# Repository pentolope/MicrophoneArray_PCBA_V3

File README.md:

# 16-channel circular PDM microphone array

A 120 mm circular, four-layer KiCad 10 carrier for sixteen `MSM261DHP006` PDM
MEMS microphones running at 3.3 V. A socketed Sipeed Tang Nano 9K performs
acquisition and decimation; a 2012 Raspberry Pi Model B collects the audio over
SPI0 over a 26-way cable to the Pi's P1 header.

The sixteen acoustic ports sit on a 54.00 mm radius at 22.5 degree intervals,
channel 0 on +X, numbered counter-clockwise viewed from the component side.

## Design summary

| | |
|---|---|
| Board | 120 mm circle, 1.6 mm, 4 layers, ENIG, green / white |
| Stackup | signal / GND / GND / signal - both inner layers solid ground |
| Microphones | 16 x `MSM261DHP006`, top-ported, 3.3 V, ports up at the rim |
| Channel pairing | adjacent channels share a data line by clock edge, 8 data nets |
| Reference clock | 24.576 MHz oscillator to a global-clock FPGA pin |
| PDM clock | 3.072 MHz, buffered to 8 series-terminated branches |
| Sample rate | 48 kHz after decimate-by-64 |
| Level translation | none - microphones, FPGA banks and Pi GPIO are all 3.3 V |
| Power | Raspberry Pi 5 V only, via PTC and series Schottky |
| Microphone supply | `LP5907MFX-3.3`, 10 uVrms, 82 dB PSRR at 1 kHz |
| Host link | SPI0, 25 MHz design target, ESD-protected and series-damped |
| Assembly | all SMT on top; module sockets and Pi header hand-soldered |

The `MSM261DHP006` is a top-ported part, so "outward-facing" is realised as
ports facing up at the rim rather than radially. The capsules are
omnidirectional, so the array response is set by the port geometry, not by
package orientation; the alternative - sixteen perpendicular daughter-cards -
cannot be assembled by JLCPCB. This is discussed in
[docs/architecture.md](docs/architecture.md).

## Documentation

- [docs/architecture.md](docs/architecture.md) - signal, clock, power and
  stackup decisions, Tang Nano 9K pin assignments, and known limitations.
- [docs/host-interface.md](docs/host-interface.md) - Raspberry Pi pinout,
  bandwidth analysis and the wire protocol.
- [docs/routing.md](docs/routing.md) - what is pre-routed and why, the
  microphone escape geometry, and how the router is driven.
- [docs/manufacturing.md](docs/manufacturing.md) - order options, order remark,
  microphone handling limits and bring-up sequence.
- [docs/timing.md](docs/timing.md) - what the interconnect timing gates
  measure on the PDM clock tree, why a net is not an electrical path, and
  which physical-stackup figures are still missing
- [docs/sources.md](docs/sources.md) - every datasheet and manufacturer rule the
  design relies on, with the facts taken from each.
- [docs/environment.md](docs/environment.md) - the Ubuntu development
  environment: which package supplies each tool, the exact versions this board
  is verified against, and why KiCad is pinned to 10.0.5.

## Repository layout

| Path | Contents |
|---|---|
| `microphone_array_v2.kicad_sch` | generated schematic - do not hand-edit |
| `microphone_array_v2.kicad_pcb` | generated board - do not hand-edit, see below |
| `microphone_array_v2.kicad_pro` | project settings, net classes, design rules |
| `MicArrayV2.kicad_sym` | generated project symbols |
| `MicArrayV2.pretty/` | project footprints: microphone, oscillator, silk-free probe pads |
| `constraints.json` | frozen requirements and manufacturing profile |
| `tools/` | design source of truth, generators and checkers |
| `docs/` | engineering documentation |
| `generated/` | reports, renders and release artefacts |

## Source of truth

`tools/netlist.py` holds the complete component list, netlist and placement.
The schematic and the board are both generated from it. Nothing about the
board is edited by hand; see [the build](#building-the-board) below. Three
independent gates keep schematic and board in step:

- `tools/check_netlist_parity.py` extracts the netlist from the generated
  schematic with `kicad-cli` and compares it against `netlist.py`, including an
  exact match on which pins are deliberately left unconnected.
- KiCad's `--schematic-parity` DRC compares the board against the schematic.
- `tools/check_placement.py` re-derives the array geometry from the board:
  every microphone's acoustic port radius and azimuth, every Tang Nano 9K
  socket pin coordinate, courtyard overlaps by exact polygon distance, JLCPCB
  package-pair body spacing, and edge clearance.

`tools/check_routes.py` adds the post-route constraints KiCad cannot express:
allowed layers per net, via budgets on the clock nets, branch length matching
across the eight microphone pairs, different-net crossings, and acid traps -
corners left with an interior angle under 90 degrees.

Regeneration commands are in [docs/manufacturing.md](docs/manufacturing.md).

## Building the board

One command, from an empty directory, start to finish:

```bash
python3 tools/build.py --install
```

It runs [tools/gen_pcb.py](tools/gen_pcb.py) to produce the pre-route board -
outline, stackup, footprints, placement, zones, net classes, rules, the
solder-mask via keep-outs and the declared critical routing, all locked - then
hands it to KiCad Routing Tools under the recorded plan in
[tools/routing_plan.json](tools/routing_plan.json), refills the zones and puts
the result through KiCad ERC, KiCad DRC, the critical-net contract and the
board's own manufacturability checks. The board is installed only if every gate
passes. Drop `--install` to build and check without touching the project.

Everything the run produced is kept in `build/`: the pre-route board, the routed
candidate, the plan that was executed, every command with its output, and the
validation reports.

Copper is never edited after routing. A failure is fixed in whichever input
caused it - the generator for placement and fanout, the rules or keep-outs for a
manufacturing violation, the critical-route generator for a clock, the routing
plan for anything else - and the board is built again from the beginning.

**Critical routing, and why each is generated rather than routed.** The
requirements come from `critical_routes` in
[constraints.json](constraints.json) and are checked after every build by
[tools/critical_nets.py](tools/critical_nets.py), which runs the validator's own
topology rule:

| Nets | Requirement | Why it is generated |
| --- | --- | --- |
| `MCLK_OSC`, `AUDIO_MCLK` | F.Cu, 0 vias | 24.576 MHz, the fastest edge on the board; a via would add a stub and a layer change in the middle of it |
| `PDM_CLK_FPGA`, `PDM_CLK_IN` | F.Cu, 0 vias | a TSSOP-20 pad row has 0.25 mm between pads, so the fan-in shape is decided by the package |
| `PDM_CLK_B0..7` | matched within 5 mm, F.Cu, 0 vias | inter-channel timing across the array; all eight are routed to one measured target |
| microphone escapes, supply ring, data spokes, ground stitching | mask keep-outs, 0.40 mm to any opening | the 0.566 mm ring corner and the plugged-via rule leave no room for a search |

## Status

**Generated, routed and DRC clean.** KiCad reports 0 DRC violations, 0
unconnected items and 0 schematic parity issues; ERC, netlist parity and the
placement audit all pass. Every via clears its nearest solder-mask opening by at
least 0.40 mm, so the board needs no filled-and-capped or resin-plugged process.
The eight PDM clock branches keep their intended topology - F.Cu only, zero
vias, and now matched to 1.1 mm rather than 24 mm - and both inner layers are
still solid ground.

Fourteen of the twenty-four test points are placed, each on top of a piece of
its own net so it needs no track of its own; the other ten have nowhere on the
top layer to go, and are listed in [docs/status.md](docs/status.md).

The fabrication outputs are committed at `generated/release/` — Gerbers, drills,
BOM, CPL, the archive, the check reports and `fabrication.json`, all built from
one board revision in a single run. They are ordinary files, so a tagged commit
stays fabricable from them years later without regenerating anything. A release
is a Git tag over such a commit, and it is not an order: JLCPCB's own part
orientations cannot be checked locally, so step through their previews before
ordering. See [docs/manufacturing.md](docs/manufacturing.md).

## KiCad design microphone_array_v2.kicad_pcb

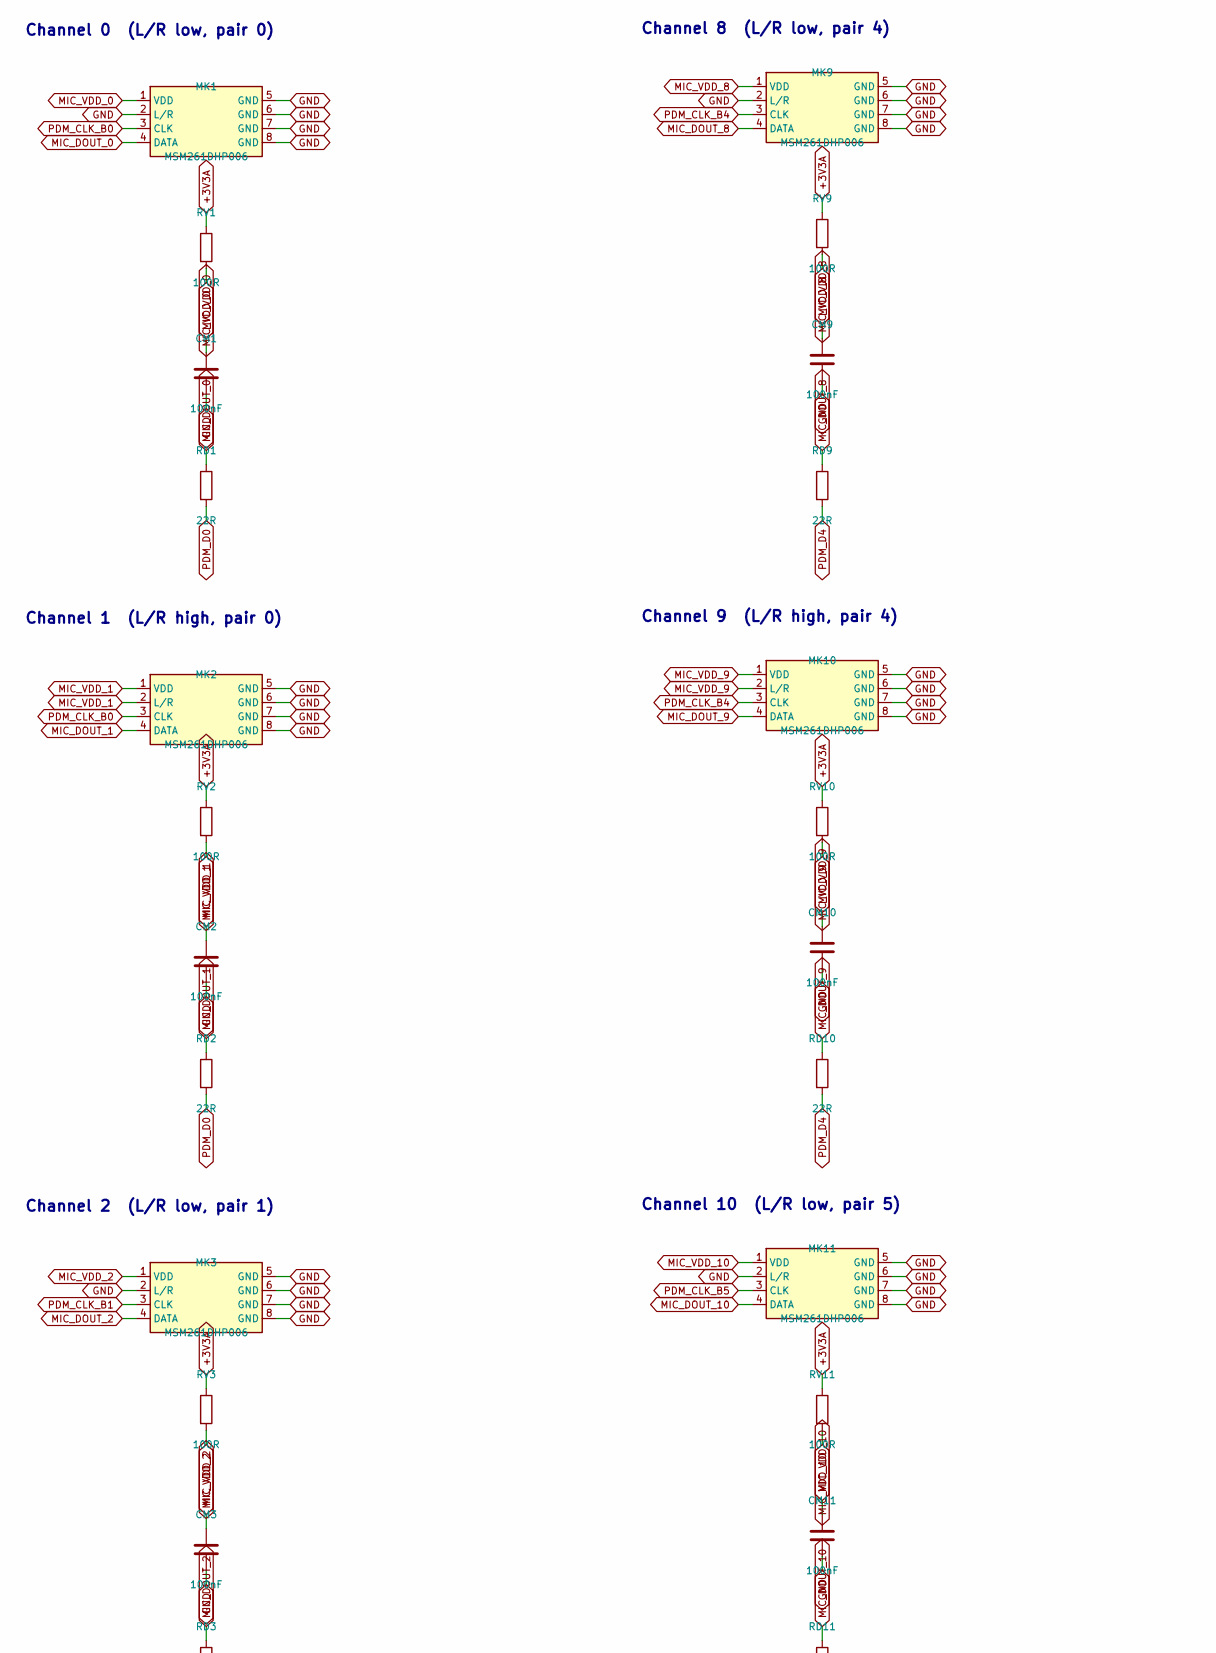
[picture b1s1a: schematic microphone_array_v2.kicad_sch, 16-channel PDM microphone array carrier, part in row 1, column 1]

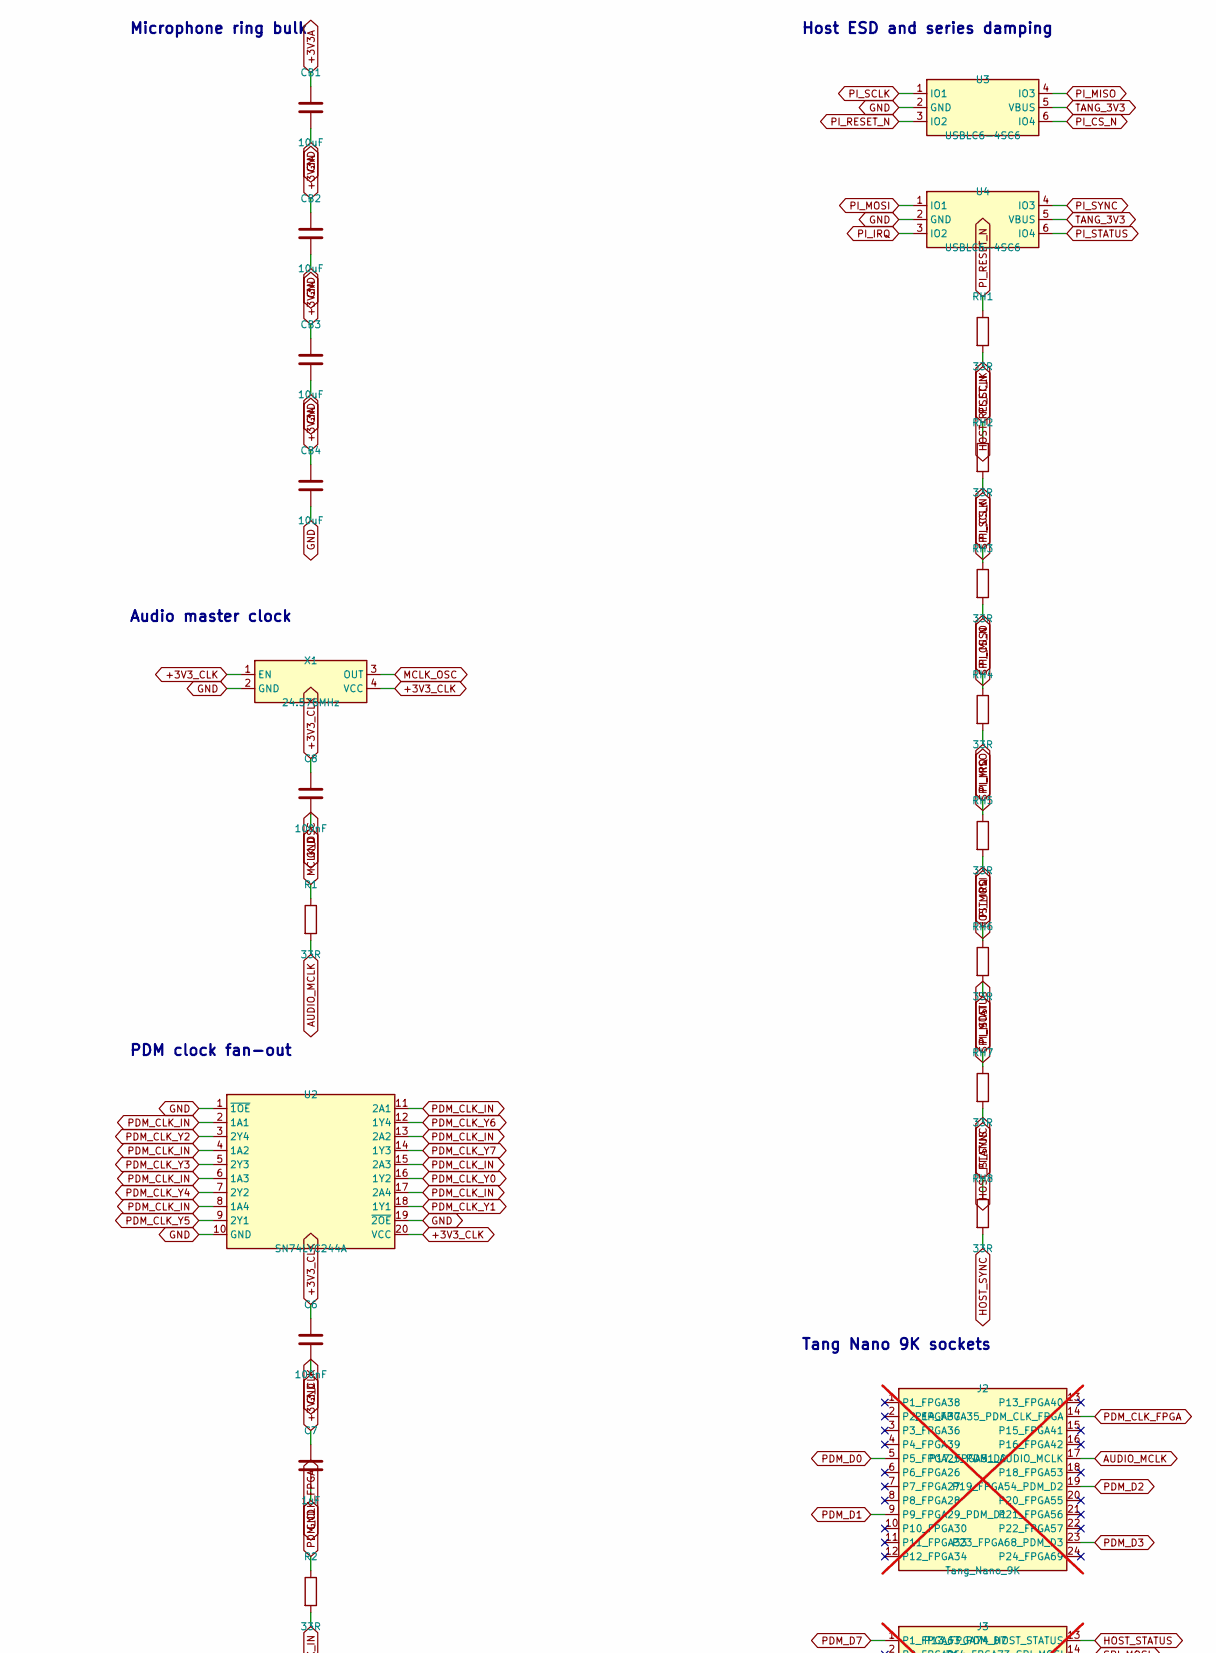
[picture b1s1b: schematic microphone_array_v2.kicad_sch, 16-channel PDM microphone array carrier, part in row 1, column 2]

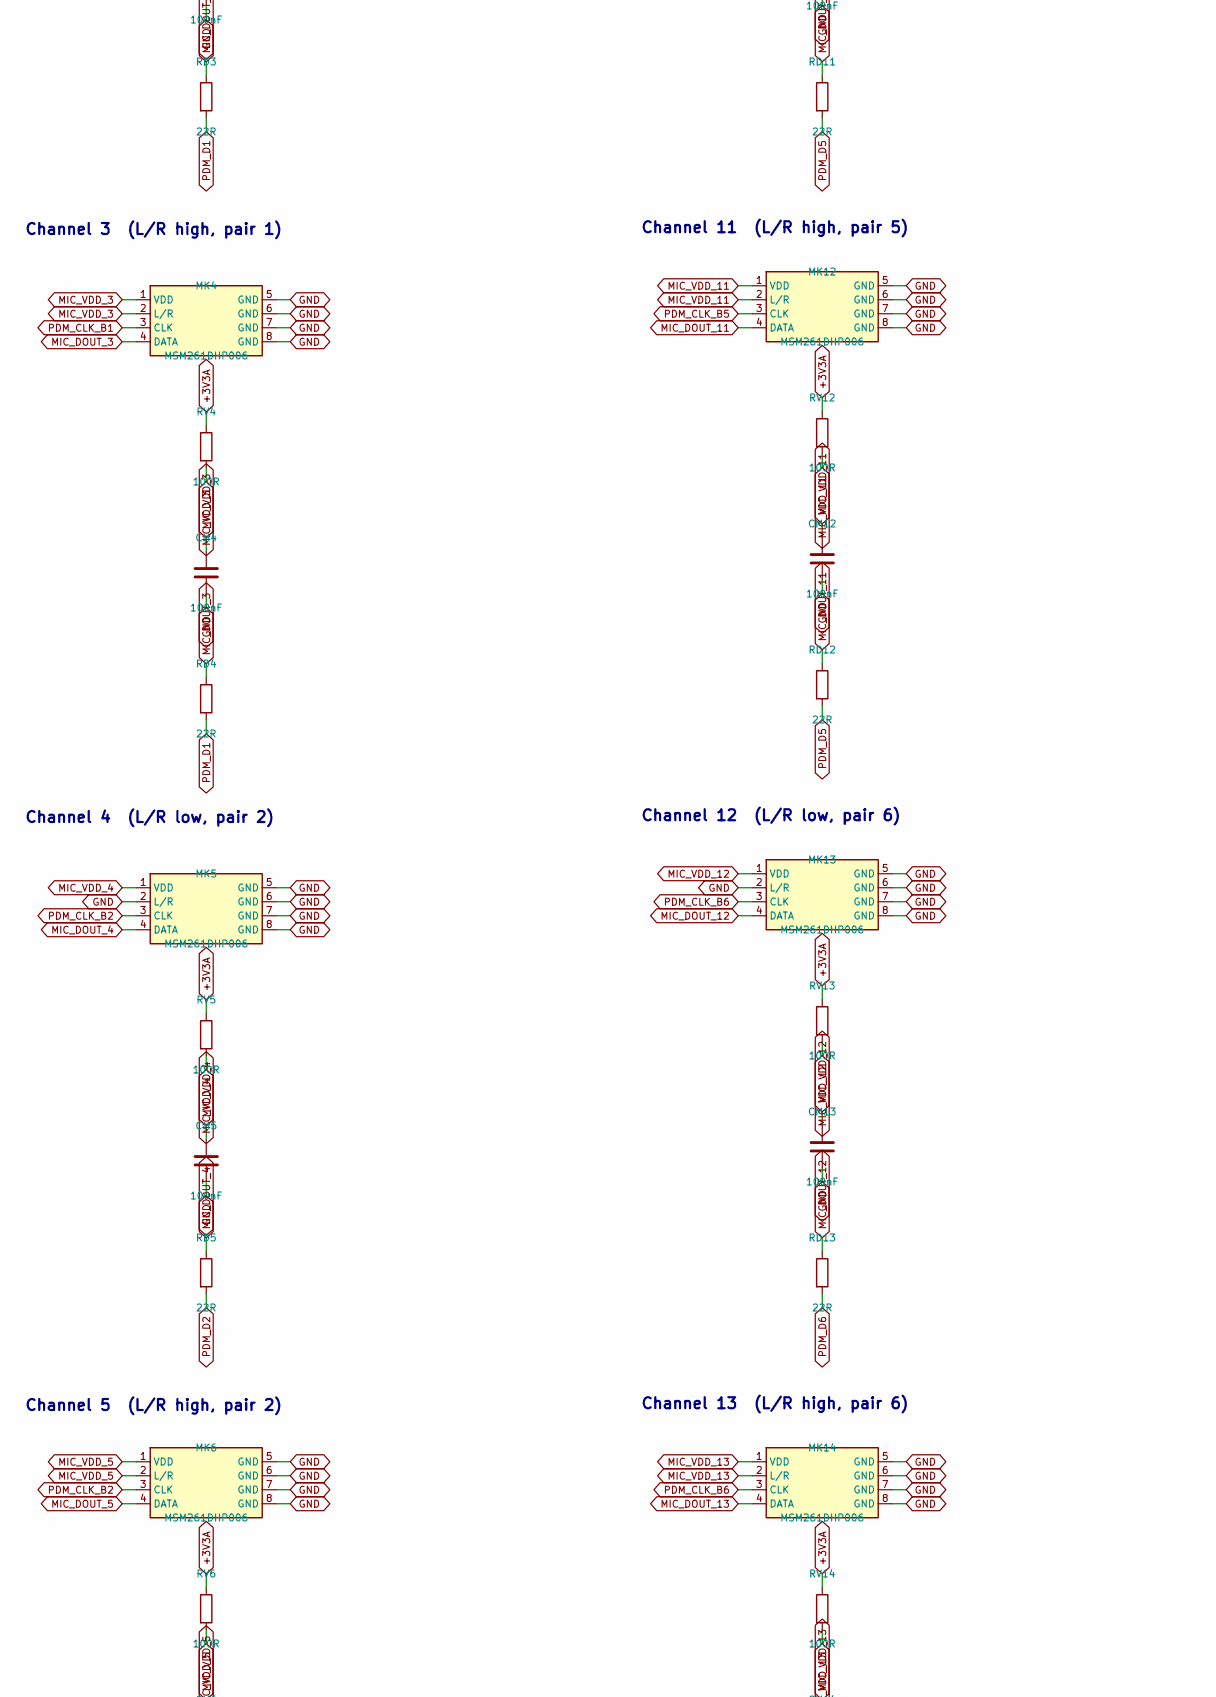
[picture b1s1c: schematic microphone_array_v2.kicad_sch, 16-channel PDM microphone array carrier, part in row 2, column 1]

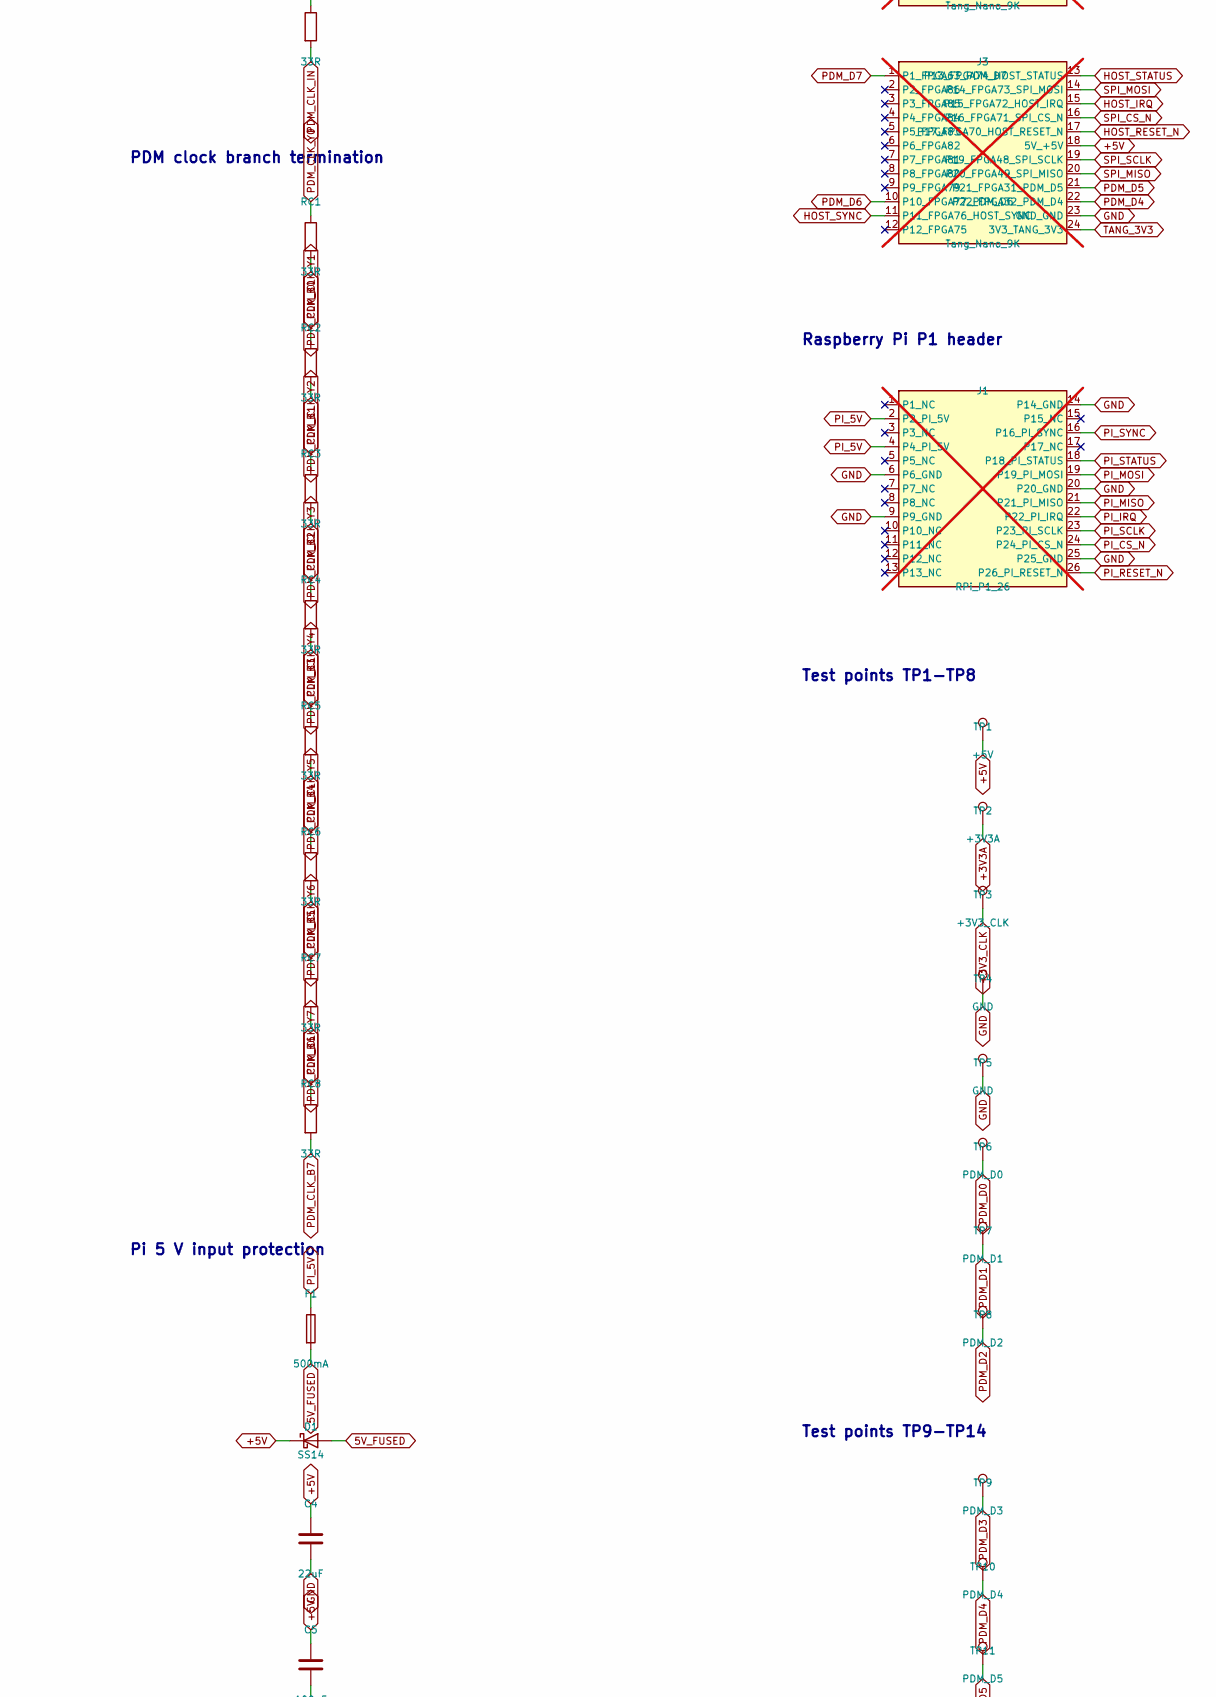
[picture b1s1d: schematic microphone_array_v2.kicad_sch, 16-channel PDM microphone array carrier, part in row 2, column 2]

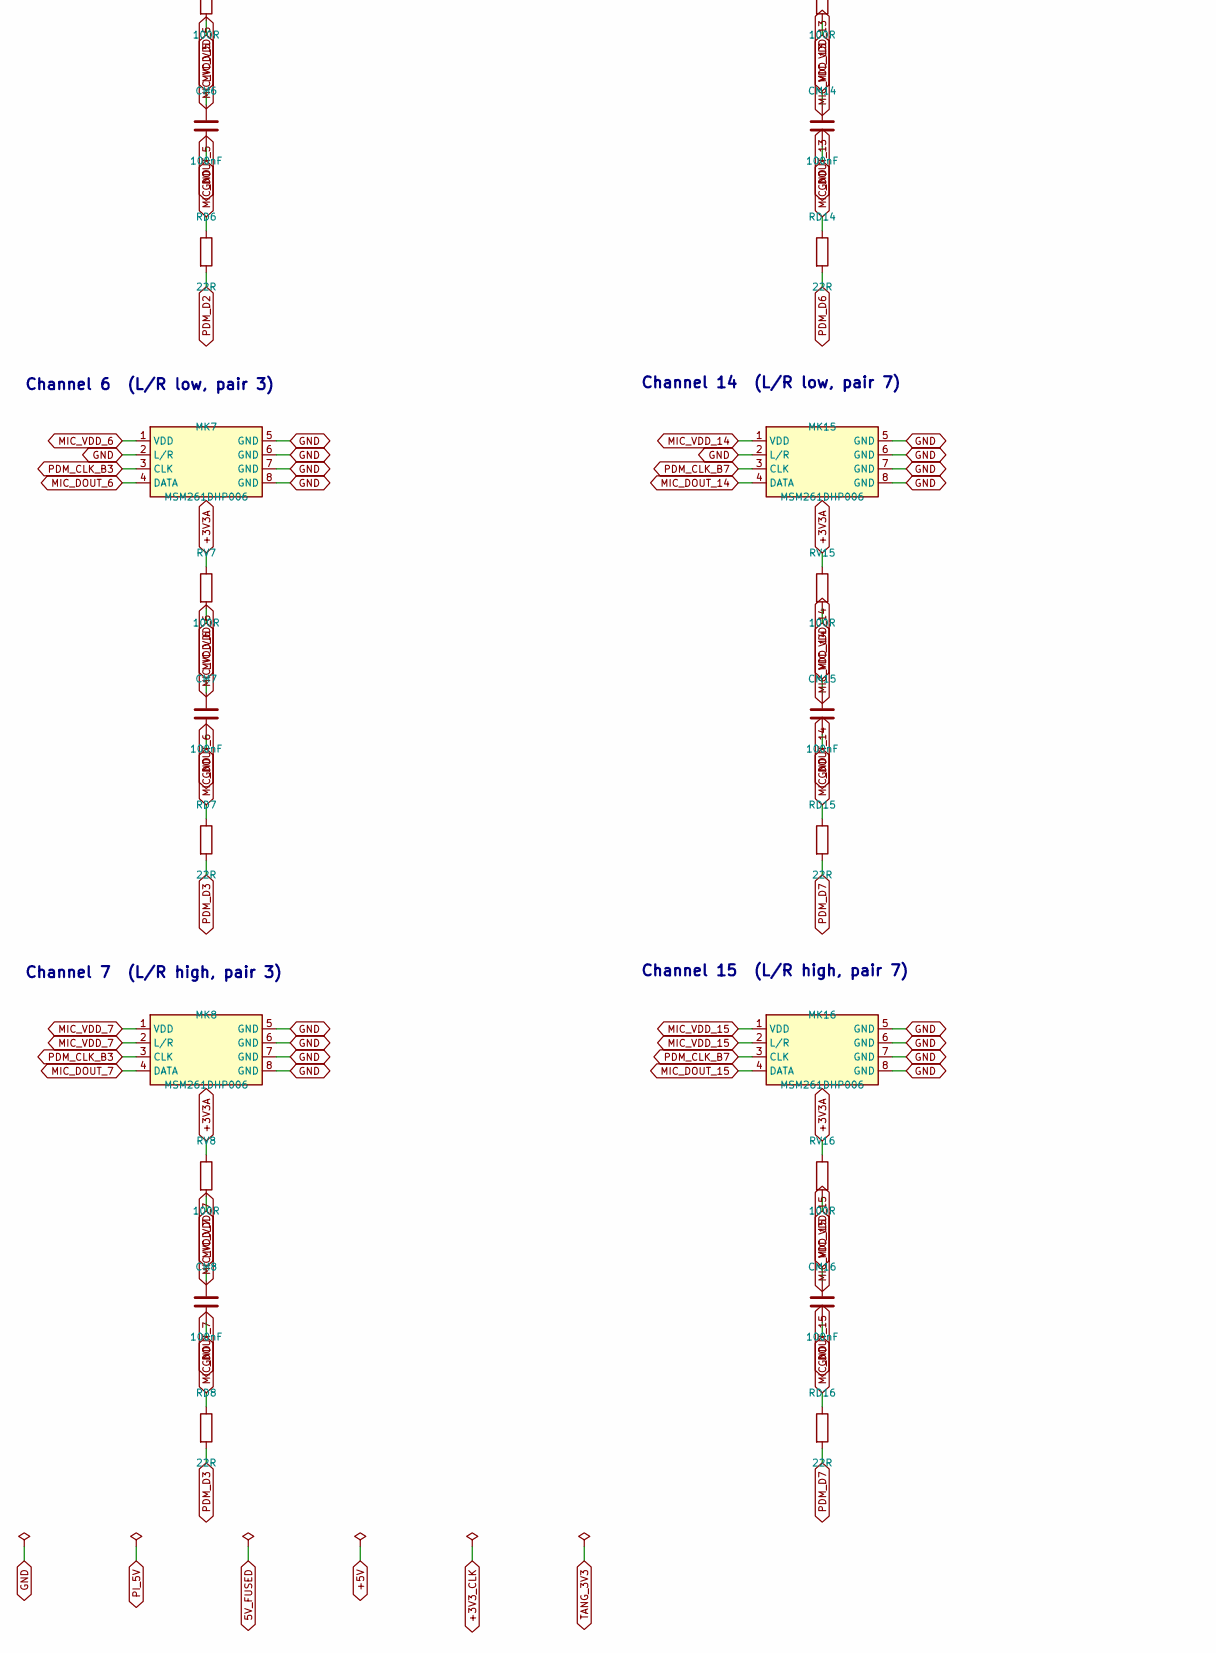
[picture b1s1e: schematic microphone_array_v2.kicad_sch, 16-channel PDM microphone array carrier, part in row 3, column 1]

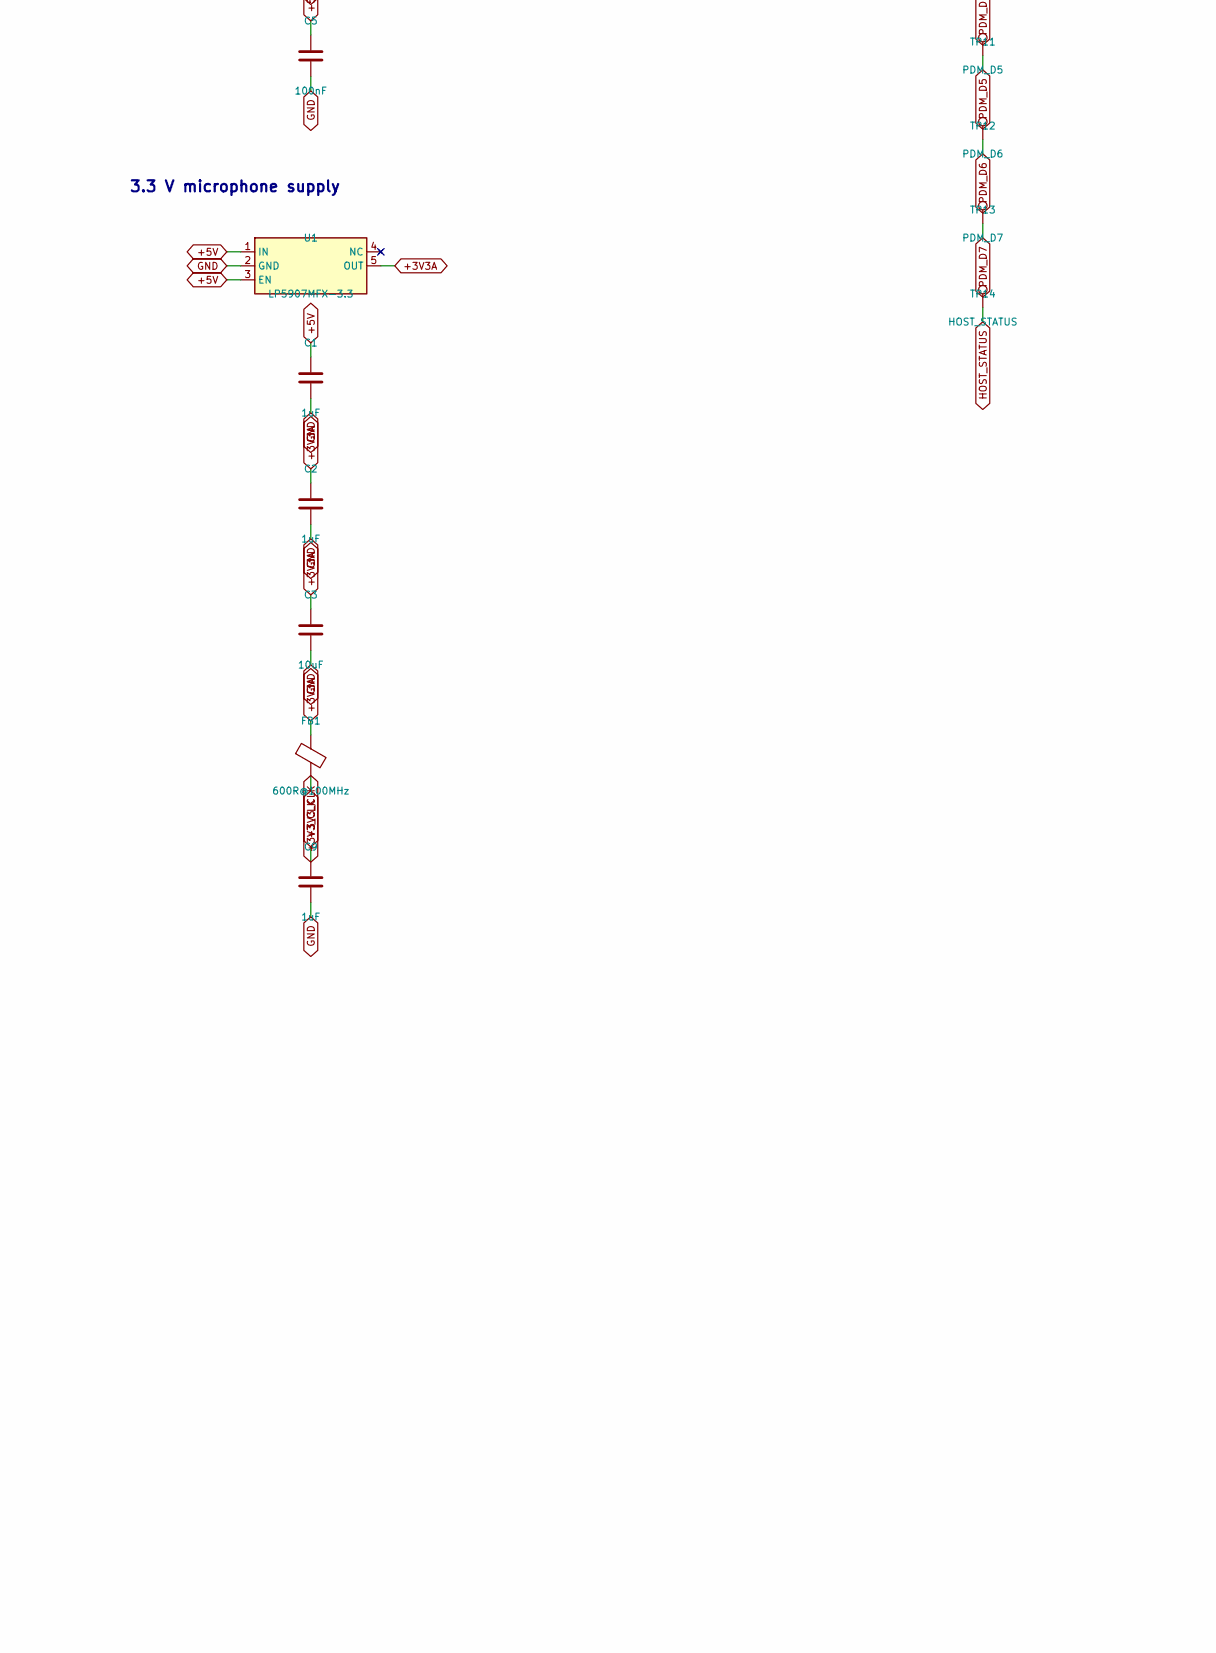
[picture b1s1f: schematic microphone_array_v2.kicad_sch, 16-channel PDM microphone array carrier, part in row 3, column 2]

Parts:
C1, C2, C7, C9: 1uF; C_0603_1608Metric; MPN CC0603KRX7R8BB105; LCSC C106858
C3: 10uF; C_0805_2012Metric; MPN CL21A106KAYNNNE; LCSC C15850
C4: 22uF; C_0805_2012Metric; MPN C2012X5R1C226KT000E; LCSC C76637
C5, C6, C8: 100nF; C_0402_1005Metric; MPN CL05B104KO5NNNC; LCSC C1525
CB1, CB2, CB3, CB4: 10uF; C_0805_2012Metric; MPN CL21A106KAYNNNE; LCSC C15850
CM1, CM2, CM3, CM4, CM5, CM6, CM7, CM8, CM9, CM10, CM11, CM12, CM13, CM14, CM15, CM16: 100nF; C_0402_1005Metric; MPN CL05B104KO5NNNC; LCSC C1525
D1: SS14; D_SMA; MPN SS14; LCSC C2480
F1: 500mA; Fuse_1812_4532Metric; MPN JK-MSMD050-30; LCSC C369168
FB1: 600R@100MHz; L_0805_2012Metric; MPN GZ2012D601TF; LCSC C1017
J1: RPi_P1_26; PinSocket_2x13_P2.54mm_Vertical; not fitted
J2, J3: Tang_Nano_9K; PinHeader_1x24_P2.54mm_Vertical; not fitted
MK1, MK2, MK3, MK4, MK5, MK6, MK7, MK8, MK9, MK10, MK11, MK12, MK13, MK14, MK15, MK16: MSM261DHP006; MSM261DHP006_LGA-8_3x4mm_TopPort; MPN MSM261DHP006; LCSC C22390138
R1, R2: 33R; R_0402_1005Metric; MPN 0402WGF330JTCE; LCSC C25105
RC1, RC2, RC3, RC4, RC5, RC6, RC7, RC8: 33R; R_0402_1005Metric; MPN 0402WGF330JTCE; LCSC C25105
RD1, RD2, RD3, RD4, RD5, RD6, RD7, RD8, RD9, RD10, RD11, RD12, RD13, RD14, RD15, RD16: 22R; R_0402_1005Metric; MPN 0402WGF220JTCE; LCSC C25092
RH1, RH2, RH3, RH4, RH5, RH6, RH7, RH8: 33R; R_0402_1005Metric; MPN 0402WGF330JTCE; LCSC C25105
RV1, RV2, RV3, RV4, RV5, RV6, RV7, RV8, RV9, RV10, RV11, RV12, RV13, RV14, RV15, RV16: 100R; R_0402_1005Metric; MPN 0402WGF1000TCE; LCSC C25076
TP1: +5V; TestPoint_Pad_D1.0mm_NoSilk
TP2: +3V3A; TestPoint_Pad_D1.5mm_NoSilk
TP3: +3V3_CLK; TestPoint_Pad_D1.5mm_NoSilk
TP4, TP5: GND; TestPoint_Pad_D1.5mm_NoSilk
TP6: PDM_D0; TestPoint_Pad_D1.5mm_NoSilk
TP7: PDM_D1; TestPoint_Pad_D1.5mm_NoSilk
TP8: PDM_D2; TestPoint_Pad_D1.5mm_NoSilk
TP9: PDM_D3; TestPoint_Pad_D1.5mm_NoSilk
TP10: PDM_D4; TestPoint_Pad_D1.5mm_NoSilk
TP11: PDM_D5; TestPoint_Pad_D1.5mm_NoSilk
TP12: PDM_D6; TestPoint_Pad_D1.5mm_NoSilk
TP13: PDM_D7; TestPoint_Pad_D1.5mm_NoSilk
TP14: HOST_STATUS; TestPoint_Pad_D1.0mm_NoSilk
U1: LP5907MFX-3.3; SOT-23-5; MPN LP5907MFX-3.3/NOPB; LCSC C80670
U2: SN74LVC244A; TSSOP-20_4.4x6.5mm_P0.65mm; MPN SN74LVC244APWR; LCSC C7668
U3, U4: USBLC6-4SC6; SOT-23-6; MPN USBLC6-4SC6; LCSC C111212
X1: 24.576MHz; Oscillator_SMD_YXC_3.2x2.5mm_4Pin; MPN OT322524.576MJBA4SL; LCSC C2831388

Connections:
5V_FUSED: D1.2 (A), F1.2
+3V3A: C2.1, C3.1, CB1.1, CB2.1, CB3.1, CB4.1, FB1.1, RV1.1, RV2.1, RV3.1, RV4.1, RV5.1, RV6.1, RV7.1, RV8.1, RV9.1, RV10.1, RV11.1, RV12.1, RV13.1, RV14.1, RV15.1, RV16.1, TP2.1, U1.5 (OUT)
+3V3_CLK: C6.1, C7.1, C8.1, C9.1, FB1.2, TP3.1, U2.20 (VCC), X1.1 (EN), X1.4 (VCC)
+5V: C1.1, C4.1, C5.1, D1.1 (K), J3.18 (5V_+5V), TP1.1, U1.1 (IN), U1.3 (EN)
AUDIO_MCLK: J2.17 (P17_FPGA51_AUDIO_MCLK), R1.2
GND: C1.2, C2.2, C3.2, C4.2, C5.2, C6.2, C7.2, C8.2, C9.2, CB1.2, CB2.2, CB3.2, CB4.2, CM1.2, CM2.2, CM3.2, CM4.2, CM5.2, CM6.2, CM7.2, CM8.2, CM9.2, CM10.2, CM11.2, CM12.2, CM13.2, CM14.2, CM15.2, CM16.2, J1.6 (P6_GND), J1.9 (P9_GND), J1.14 (P14_GND), J1.20 (P20_GND), J1.25 (P25_GND), J3.23 (GND_GND), MK1.2 (L/R), MK1.5 (GND), MK1.6 (GND), MK1.7 (GND), MK1.8 (GND), MK2.5 (GND), MK2.6 (GND), MK2.7 (GND), MK2.8 (GND), MK3.2 (L/R), MK3.5 (GND), MK3.6 (GND), MK3.7 (GND), MK3.8 (GND), MK4.5 (GND), MK4.6 (GND), MK4.7 (GND), MK4.8 (GND), MK5.2 (L/R), MK5.5 (GND), MK5.6 (GND), MK5.7 (GND), MK5.8 (GND), MK6.5 (GND), MK6.6 (GND), MK6.7 (GND), MK6.8 (GND), MK7.2 (L/R), MK7.5 (GND), MK7.6 (GND), MK7.7 (GND), MK7.8 (GND), MK8.5 (GND), MK8.6 (GND), MK8.7 (GND), MK8.8 (GND), MK9.2 (L/R), MK9.5 (GND), MK9.6 (GND), MK9.7 (GND), MK9.8 (GND), MK10.5 (GND), MK10.6 (GND), MK10.7 (GND), MK10.8 (GND), MK11.2 (L/R), MK11.5 (GND), MK11.6 (GND), MK11.7 (GND), MK11.8 (GND), MK12.5 (GND), MK12.6 (GND), MK12.7 (GND), MK12.8 (GND), MK13.2 (L/R), MK13.5 (GND), MK13.6 (GND), MK13.7 (GND), MK13.8 (GND), MK14.5 (GND), MK14.6 (GND), MK14.7 (GND), MK14.8 (GND), MK15.2 (L/R), MK15.5 (GND), MK15.6 (GND), MK15.7 (GND), MK15.8 (GND), MK16.5 (GND), MK16.6 (GND), MK16.7 (GND), MK16.8 (GND), TP4.1, TP5.1, U1.2 (GND), U2.1 (~1OE), U2.10 (GND), U2.19 (~2OE), U3.2 (GND), U4.2 (GND), X1.2 (GND)
HOST_IRQ: J3.15 (P15_FPGA72_HOST_IRQ), RH5.2
HOST_RESET_N: J3.17 (P17_FPGA70_HOST_RESET_N), RH1.2
HOST_STATUS: J3.13 (P13_FPGA74_HOST_STATUS), RH7.2, TP14.1
HOST_SYNC: J3.11 (P11_FPGA76_HOST_SYNC), RH8.2
MCLK_OSC: R1.1, X1.3 (OUT)
MIC_DOUT_0: MK1.4 (DATA), RD1.1
MIC_DOUT_1: MK2.4 (DATA), RD2.1
MIC_DOUT_2: MK3.4 (DATA), RD3.1
MIC_DOUT_3: MK4.4 (DATA), RD4.1
MIC_DOUT_4: MK5.4 (DATA), RD5.1
MIC_DOUT_5: MK6.4 (DATA), RD6.1
MIC_DOUT_6: MK7.4 (DATA), RD7.1
MIC_DOUT_7: MK8.4 (DATA), RD8.1
MIC_DOUT_8: MK9.4 (DATA), RD9.1
MIC_DOUT_9: MK10.4 (DATA), RD10.1
MIC_DOUT_10: MK11.4 (DATA), RD11.1
MIC_DOUT_11: MK12.4 (DATA), RD12.1
MIC_DOUT_12: MK13.4 (DATA), RD13.1
MIC_DOUT_13: MK14.4 (DATA), RD14.1
MIC_DOUT_14: MK15.4 (DATA), RD15.1
MIC_DOUT_15: MK16.4 (DATA), RD16.1
MIC_VDD_0: CM1.1, MK1.1 (VDD), RV1.2
MIC_VDD_1: CM2.1, MK2.1 (VDD), MK2.2 (L/R), RV2.2
MIC_VDD_2: CM3.1, MK3.1 (VDD), RV3.2
MIC_VDD_3: CM4.1, MK4.1 (VDD), MK4.2 (L/R), RV4.2
MIC_VDD_4: CM5.1, MK5.1 (VDD), RV5.2
MIC_VDD_5: CM6.1, MK6.1 (VDD), MK6.2 (L/R), RV6.2
MIC_VDD_6: CM7.1, MK7.1 (VDD), RV7.2
MIC_VDD_7: CM8.1, MK8.1 (VDD), MK8.2 (L/R), RV8.2
MIC_VDD_8: CM9.1, MK9.1 (VDD), RV9.2
MIC_VDD_9: CM10.1, MK10.1 (VDD), MK10.2 (L/R), RV10.2
MIC_VDD_10: CM11.1, MK11.1 (VDD), RV11.2
MIC_VDD_11: CM12.1, MK12.1 (VDD), MK12.2 (L/R), RV12.2
MIC_VDD_12: CM13.1, MK13.1 (VDD), RV13.2
MIC_VDD_13: CM14.1, MK14.1 (VDD), MK14.2 (L/R), RV14.2
MIC_VDD_14: CM15.1, MK15.1 (VDD), RV15.2
MIC_VDD_15: CM16.1, MK16.1 (VDD), MK16.2 (L/R), RV16.2
PDM_CLK_B0: MK1.3 (CLK), MK2.3 (CLK), RC1.2
PDM_CLK_B1: MK3.3 (CLK), MK4.3 (CLK), RC2.2
PDM_CLK_B2: MK5.3 (CLK), MK6.3 (CLK), RC3.2
PDM_CLK_B3: MK7.3 (CLK), MK8.3 (CLK), RC4.2
PDM_CLK_B4: MK9.3 (CLK), MK10.3 (CLK), RC5.2
PDM_CLK_B5: MK11.3 (CLK), MK12.3 (CLK), RC6.2
PDM_CLK_B6: MK13.3 (CLK), MK14.3 (CLK), RC7.2
PDM_CLK_B7: MK15.3 (CLK), MK16.3 (CLK), RC8.2
PDM_CLK_FPGA: J2.14 (P14_FPGA35_PDM_CLK_FPGA), R2.1
PDM_CLK_IN: R2.2, U2.2 (1A1), U2.4 (1A2), U2.6 (1A3), U2.8 (1A4), U2.11 (2A1), U2.13 (2A2), U2.15 (2A3), U2.17 (2A4)
PDM_CLK_Y0: RC1.1, U2.16 (1Y2)
PDM_CLK_Y1: RC2.1, U2.18 (1Y1)
PDM_CLK_Y2: RC3.1, U2.3 (2Y4)
PDM_CLK_Y3: RC4.1, U2.5 (2Y3)
PDM_CLK_Y4: RC5.1, U2.7 (2Y2)
PDM_CLK_Y5: RC6.1, U2.9 (2Y1)
PDM_CLK_Y6: RC7.1, U2.12 (1Y4)
PDM_CLK_Y7: RC8.1, U2.14 (1Y3)
PDM_D0: J2.5 (P5_FPGA25_PDM_D0), RD1.2, RD2.2, TP6.1
PDM_D1: J2.9 (P9_FPGA29_PDM_D1), RD3.2, RD4.2, TP7.1
PDM_D2: J2.19 (P19_FPGA54_PDM_D2), RD5.2, RD6.2, TP8.1
PDM_D3: J2.23 (P23_FPGA68_PDM_D3), RD7.2, RD8.2, TP9.1
PDM_D4: J3.22 (P22_FPGA32_PDM_D4), RD9.2, RD10.2, TP10.1
PDM_D5: J3.21 (P21_FPGA31_PDM_D5), RD11.2, RD12.2, TP11.1
PDM_D6: J3.10 (P10_FPGA77_PDM_D6), RD13.2, RD14.2, TP12.1
PDM_D7: J3.1 (P1_FPGA63_PDM_D7), RD15.2, RD16.2, TP13.1
PI_5V: F1.1, J1.2 (P2_PI_5V), J1.4 (P4_PI_5V)
PI_CS_N: J1.24 (P24_PI_CS_N), RH3.1, U3.6 (IO4)
PI_IRQ: J1.22 (P22_PI_IRQ), RH5.1, U4.3 (IO2)
PI_MISO: J1.21 (P21_PI_MISO), RH4.1, U3.4 (IO3)
PI_MOSI: J1.19 (P19_PI_MOSI), RH6.1, U4.1 (IO1)
PI_RESET_N: J1.26 (P26_PI_RESET_N), RH1.1, U3.3 (IO2)
PI_SCLK: J1.23 (P23_PI_SCLK), RH2.1, U3.1 (IO1)
PI_STATUS: J1.18 (P18_PI_STATUS), RH7.1, U4.6 (IO4)
PI_SYNC: J1.16 (P16_PI_SYNC), RH8.1, U4.4 (IO3)
SPI_CS_N: J3.16 (P16_FPGA71_SPI_CS_N), RH3.2
SPI_MISO: J3.20 (P20_FPGA49_SPI_MISO), RH4.2
SPI_MOSI: J3.14 (P14_FPGA73_SPI_MOSI), RH6.2
SPI_SCLK: J3.19 (P19_FPGA48_SPI_SCLK), RH2.2
TANG_3V3: J3.24 (3V3_TANG_3V3), U3.5 (VBUS), U4.5 (VBUS)

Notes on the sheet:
Channel 0 (L/R low, pair 0)
Channel 1 (L/R high, pair 0)
Channel 2 (L/R low, pair 1)
Channel 3 (L/R high, pair 1)
Channel 4 (L/R low, pair 2)
Channel 5 (L/R high, pair 2)
Channel 6 (L/R low, pair 3)
Channel 7 (L/R high, pair 3)
Channel 8 (L/R low, pair 4)
Channel 9 (L/R high, pair 4)
Channel 10 (L/R low, pair 5)
Channel 11 (L/R high, pair 5)
Channel 12 (L/R low, pair 6)
Channel 13 (L/R high, pair 6)
Channel 14 (L/R low, pair 7)
Channel 15 (L/R high, pair 7)
Microphone ring bulk
Audio master clock
PDM clock fan-out
PDM clock branch termination
Pi 5 V input protection
3.3 V microphone supply
Host ESD and series damping
Tang Nano 9K sockets
Raspberry Pi P1 header
Test points TP1-TP8
Test points TP9-TP14
